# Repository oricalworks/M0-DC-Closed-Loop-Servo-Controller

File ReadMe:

Circuit Pro Industries M0 DC Closed Loop Servo

   read a rotary encoder with interrupts
   Encoder hooked up with common to GROUND,
   encoder0PinA to pin 2, encoder0PinB to pin 4 (or pin 3 see below)
   it doesn't matter which encoder pin you use for A or B 
   
   is possible to change PID costants by sending on SerialUSB interfaces the values separated by ',' in this order: KP,KD,KI
   example: 5.2,3.1,0 so we have  KP=5.2 KD=3.1 KI=0 is only for testing purposes, but i will leave this function with eeprom storage

*/ 
/*   -----------------To Do-----------------
 *
 *    Come up with offical name!!!!!
 *    Implement code for physical EEPROM for V2 Board (Chip:24LC256 ADDRESS:0x50) (32Kb Storage) (I2c on SDA and SCL)
 *    PID Auto Tune
 *    Error Reporting
 *    Force sensing
 *    Host Communincation
 *    Performance Reporting and Info for Osiliscope
 *    Switchless Homing(force sensing)
 *    Master and Slave Mirroring
 *    Configurable Limits
 *    Create Host Software
 *    Implement Unit linking
 *    Implement Wire communication (Serial I2C)
 *    Complete data sheet and usage guide.
 *    
*/

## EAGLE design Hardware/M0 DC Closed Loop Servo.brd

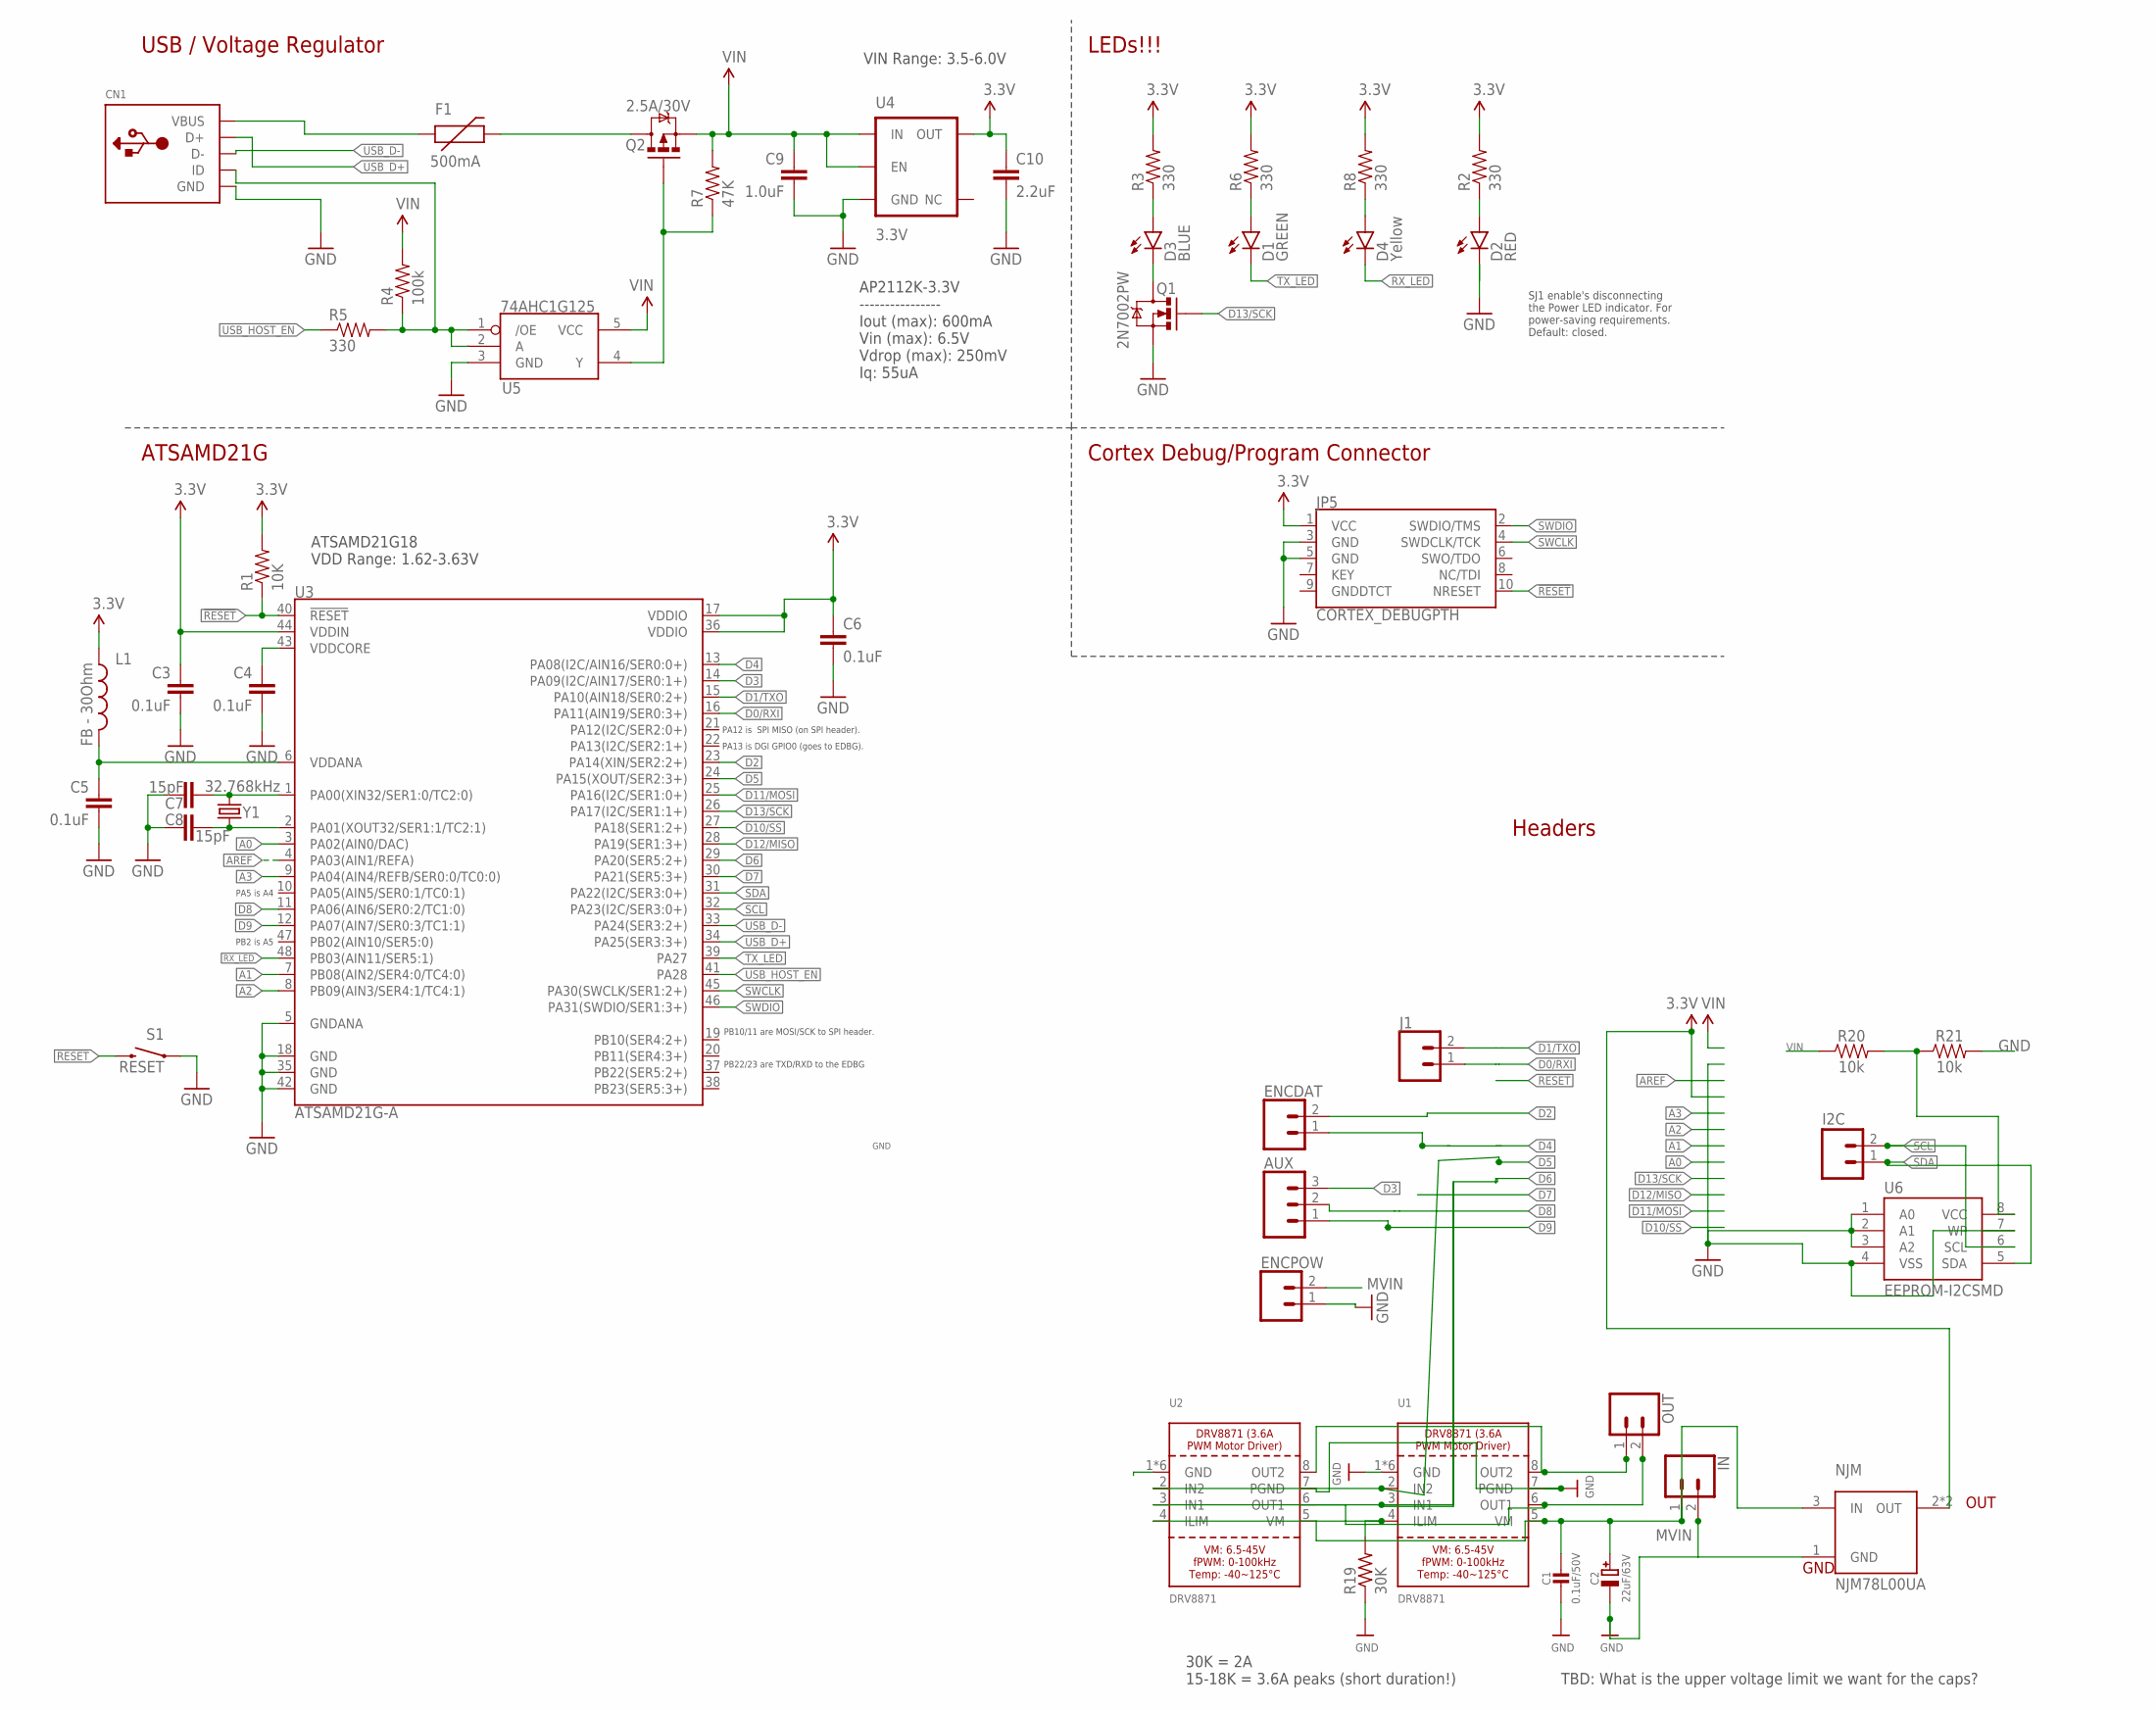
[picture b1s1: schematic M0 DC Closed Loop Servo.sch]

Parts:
AUX: CONN_03LONGPADS; 1X03_LONGPADS
C1: 0.1uF/50V; 0805-NO
C2: 22uF/63V; PANASONIC_D
C3, C4, C5, C6: 0.1uF; 0402-CAP
C7, C8: 15pF; 0402-CAP
C9: 1.0uF; 0805-CAP
C10: 2.2uF; 0603-CAP
CN1: USBMINIB; USB-MINIB
D1: GREEN; LED-0603
D2: RED; LED-0603
D3: BLUE; LED-0603
D4: Yellow; LED-0603
ENCDAT: CONN_02; 1X02
ENCPOW: CONN_02; 1X02
F1: 500mA; PTC-1206
I2C: M021X02_NO_SILK; 1X02_NO_SILK@1
IN: CONN_02PTH3; 1X02_LONGPADS
J1: CONN_02; 1X02
JP5: CORTEX_DEBUGPTH; 2X5-PTH-1.27MM
L1: FB - 30Ohm; 0603
NJM: NJM78L00UA; SOT89
OUT: CONN_02PTH3; 1X02_LONGPADS
Q1: 2N7002PW; SOT323
Q2: 2.5A/30V; SOT23-3
R1: 10K; 0603-RES
R2, R3, R5, R6, R8: 330; 0603-RES
R4: 100k; 0603-RES
R7: 47K; 0603-RES
R19: 30K; 0805-THM
R20, R21: 10k; 0603
S1: RESET; TACTILE_SWITCH_SMD_4.6X2.8MM
U1, U2: DRV8871; HSOP8
U3: ATSAMD21G-A; TQFP-48
U4: 3.3V; SOT23-5
U5: 74AHC1G125; SOT23-5
U6: EEPROM-I2CSMD; SO08
Y1: 32.768kHz; CRYSTAL-SMD-3.2X1.5MM

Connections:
3.3V: C3.1, C6.1, C10.1, JP5.1 (VCC), L1.1, NJM.2 (OUT), NJM.2@1 (OUT), R1.2, R2.2, R3.2, R6.2, R8.2, U3.17 (VDDIO), U3.36 (VDDIO), U3.44 (VDDIN), U4.5 (OUT)
!RESET: JP5.10 (NRESET), R1.1, S1.3 (2), S1.4 (2), U3.40 (!RESET!)
A0: U3.3 (PA02(AIN0/DAC))
A1: U3.7 (PB08(AIN2/SER4:0/TC4:0))
A2: U3.8 (PB09(AIN3/SER4:1/TC4:1))
A3: U3.9 (PA04(AIN4/REFB/SER0:0/TC0:0))
AREF: U3.4 (PA03(AIN1/REFA))
D0/RXI: J1.1, U3.16 (PA11(AIN19/SER0:3+))
D1/TXO: J1.2, U3.15 (PA10(AIN18/SER0:2+))
D2: ENCDAT.2, U3.23 (PA14(XIN/SER2:2+))
D3: AUX.3, U3.14 (PA09(I2C/AIN17/SER0:1+))
D4: ENCDAT.1, U3.13 (PA08(I2C/AIN16/SER0:0+))
D5: U1.2 (IN2), U2.2 (IN2), U3.24 (PA15(XOUT/SER2:3+))
D6: U1.3 (IN1), U2.3 (IN1), U3.29 (PA20(SER5:2+))
D7: U3.30 (PA21(SER5:3+))
D8: AUX.2, U3.11 (PA06(AIN6/SER0:2/TC1:0))
D9: AUX.1, U3.12 (PA07(AIN7/SER0:3/TC1:1))
D10/SS: U3.27 (PA18(SER1:2+))
D11/MOSI: U3.25 (PA16(I2C/SER1:0+))
D12/MISO: U3.28 (PA19(SER1:3+))
D13/SCK: Q1.1 (G), U3.26 (PA17(I2C/SER1:1+))
GND: C1.2, C2.-, C3.2, C4.2, C5.2, C6.2, C7.1, C8.2, C9.2, C10.2, CN1.GND, ENCPOW.1, IN.2, JP5.3 (GND), JP5.5 (GND), NJM.1 (GND), Q1.2 (S), R19.1, R21.2, S1.1, S1.2 (1), U1.1 (GND), U1.7 (PGND), U1.GND, U1.P$1 (GND), U1.P$2 (GND), U1.P$3 (GND), U1.P$4 (GND), U2.1 (GND), U2.7 (PGND), U2.GND, U2.P$1 (GND), U2.P$2 (GND), U2.P$3 (GND), U2.P$4 (GND), U3.5 (GNDANA), U3.18 (GND), U3.35 (GND), U3.42 (GND), U4.2 (GND), U5.3 (GND), U6.1 (A0), U6.2 (A1), U6.3 (A2), U6.4 (VSS), U6.7 (WP)
MVIN: C1.1, C2.+, ENCPOW.2, IN.1, NJM.3 (IN), U1.5 (VM), U2.5 (VM)
unnamed: CN1.VBUS, F1.1
unnamed: C7.2, U3.1 (PA00(XIN32/SER1:0/TC2:0)), Y1.P$2 (2)
unnamed: D3.C, Q1.3 (D)
unnamed: C8.1, U3.2 (PA01(XOUT32/SER1:1/TC2:1)), Y1.P$1 (1)
unnamed: D2.A, R2.1
unnamed: D3.A, R3.1
unnamed: F1.2, Q2.3 (D)
unnamed: CN1.ID, R4.1, R5.2, U5.1 (/OE), U5.2 (A)
unnamed: Q2.1 (G), R7.1, U5.4 (Y)
unnamed: D1.A, R6.1
unnamed: D4.A, R8.1
unnamed: R20.2, R21.1, U6.8 (VCC)
unnamed: R19.2, U1.4 (ILIM), U2.4 (ILIM)
OUT1: OUT.2, U1.6 (OUT1), U2.6 (OUT1)
OUT2: OUT.1, U1.8 (OUT2), U2.8 (OUT2)
RX_LED: D4.C, U3.48 (PB03(AIN11/SER5:1))
SCL: I2C.2, U3.32 (PA23(I2C/SER3:0+)), U6.6 (SCL)
SDA: I2C.1, U3.31 (PA22(I2C/SER3:0+)), U6.5 (SDA)
SWCLK: JP5.4 (SWDCLK/TCK), U3.45 (PA30(SWCLK/SER1:2+))
SWDIO: JP5.2 (SWDIO/TMS), U3.46 (PA31(SWDIO/SER1:3+))
TX_LED: D1.C, U3.39 (PA27)
USB_D+: CN1.D+, U3.34 (PA25(SER3:3+))
USB_D-: CN1.D-, U3.33 (PA24(SER3:2+))
USB_HOST_EN: R5.1, U3.41 (PA28)
VDDANA: C5.1, L1.2, U3.6 (VDDANA)
VDDCORE: C4.1, U3.43 (VDDCORE)
VIN: C9.1, Q2.2 (S), R4.2, R7.2, R20.1, U4.1 (IN), U4.3 (EN), U5.5 (VCC)

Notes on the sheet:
PB22/23 are TXD/RXD to the EDBG
PB10/11 are MOSI/SCK to SPI header.
PA12 is SPI MISO (on SPI header).
PA13 is DGI GPIO0 (goes to EDBG).
PA5 is A4
PB2 is A5
USB / Voltage Regulator
LEDs!!!
Cortex Debug/Program Connector
Headers
ATSAMD21G
ATSAMD21G18 VDD Range: 1.62-3.63V
SJ1 enable's disconnecting the Power LED indicator. For power-saving requirements. Default: closed.
VIN Range: 3.5-6.0V
AP2112K-3.3V ---------------- Iout (max): 600mA Vin (max): 6.5V Vdrop (max): 250mV Iq: 55uA
TBD: What is the upper voltage limit we want for the caps?
30K = 2A 15-18K = 3.6A peaks (short duration!)
GND
OUT

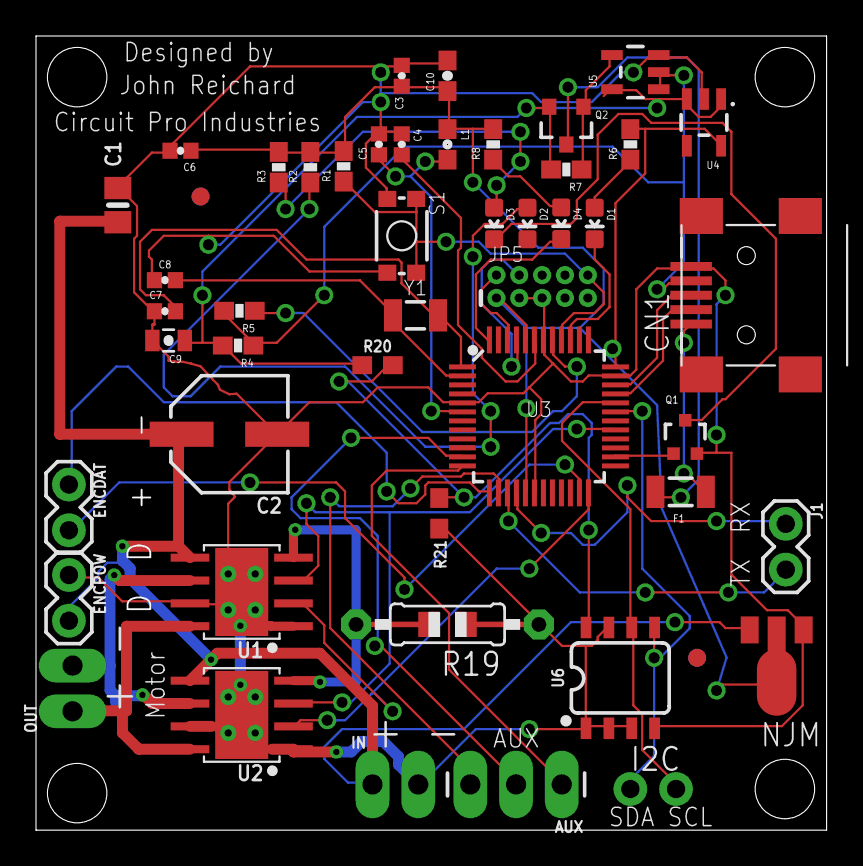
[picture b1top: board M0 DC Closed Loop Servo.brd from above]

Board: 2 copper layers, 43.9 x 44.1 mm, 49 parts (0 on the bottom side), 41 nets.

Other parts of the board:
U$7, U$8: CIRCLE-1MM-3R

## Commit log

2017-10-03 Added Firmware and Hardware
    Added Firmware and Hardware
2017-10-03 Created Read Me
2017-10-03 Updated File Structure for IDE
2017-10-03 Structure update
2017-10-04 V2 Board Update
2017-10-04 Added Thermal Vias and Pads
2017-10-04 Hardware Release V2
2017-10-11 Code Updated and Data Sheet Created
    Code Updated and Data Sheet Created
2017-10-11 Started Usage Information
2017-10-12 Updated Data Sheet
    Need To come Up with and official name to for the board rather than
    SPEC name
2017-11-07 Mega Update
2017-11-11 fixed trace collision
2017-11-30 Board Redesign, Rework, and Overhaul to V2
    Board Redesign, Rework, and Overhaul to V2
2017-12-01 Board Clean UP
2017-12-01 COMPLETE OVER HULL
2017-12-05 rey-load

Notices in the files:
parts and their libraries:
microbuilder: This work is placed in the public domain, and may be freely used for commercial and non-commercial work with the following conditions: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
SparkFun-Capacitors: Licensing: Creative Commons ShareAlike 4.0 International - https://creativecommons.org/licenses/by-sa/4.0
